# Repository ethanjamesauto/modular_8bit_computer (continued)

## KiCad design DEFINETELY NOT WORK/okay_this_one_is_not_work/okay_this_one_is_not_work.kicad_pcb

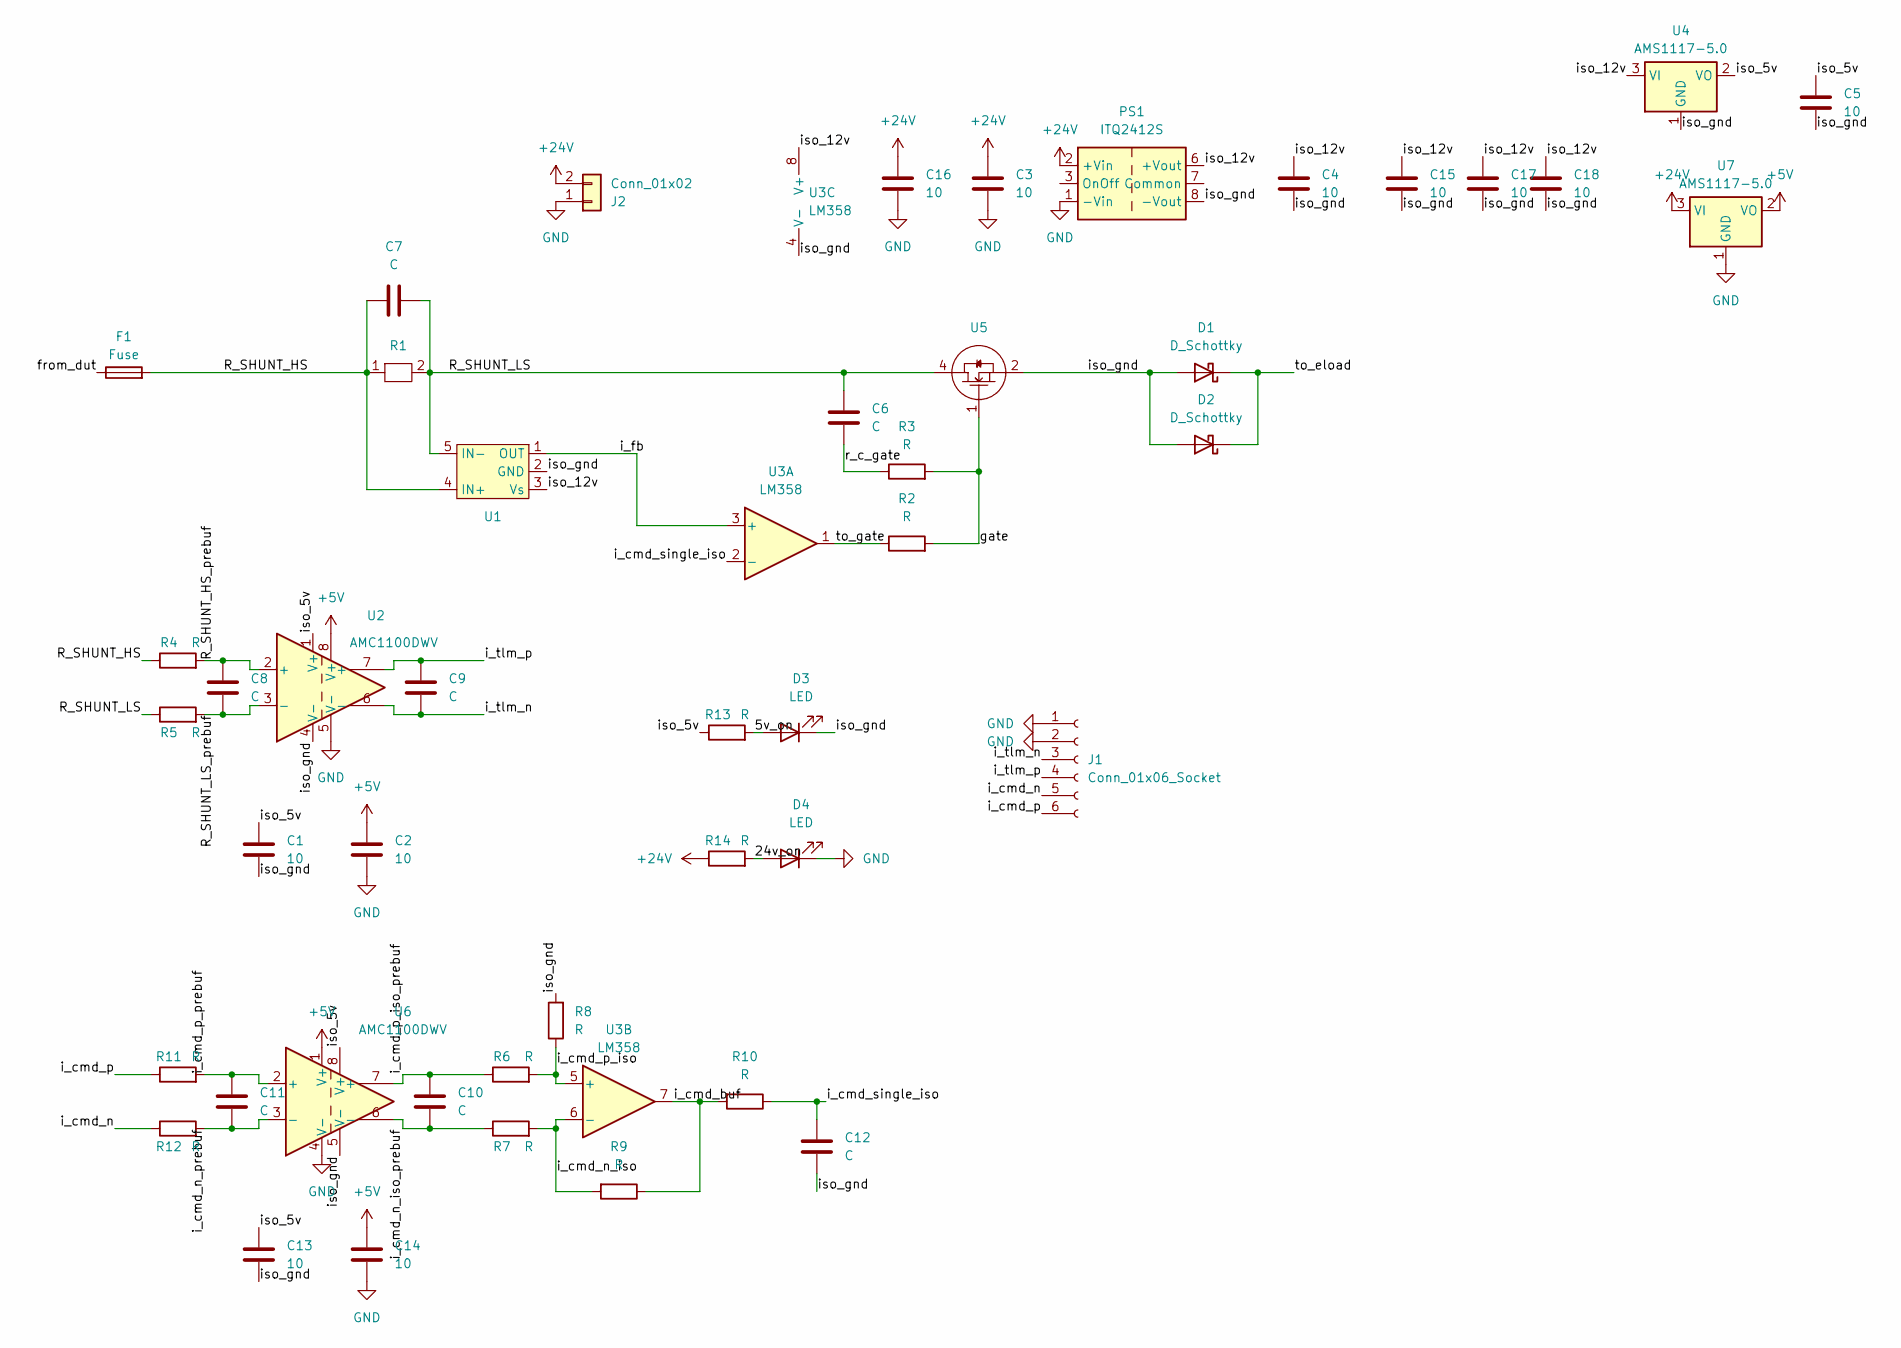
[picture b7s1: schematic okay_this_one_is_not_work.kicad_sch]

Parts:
C1, C2, C3, C4, C5, C13, C14, C15, C16, C17, C18: 10; C_1206_3216Metric_Pad1.33x1.80mm_HandSolder
C6, C7, C8, C9, C10, C11, C12: C; C_0603_1608Metric_Pad1.08x0.95mm_HandSolder
D1, D2: D_Schottky; D_PowerDI-5
D3, D4: LED; LED_0603_1608Metric_Pad1.05x0.95mm_HandSolder
F1: Fuse; Fuse_Schurter_UMT250
J1: Conn_01x06_Socket; PinHeader_1x06_P2.54mm_Vertical
J2: Conn_01x02; PhoenixContact_SPT_2.5_2-H-5.0_1x02_P5.0mm_Horizontal
PS1: ITQ2412S; Converter_DCDC_XP_POWER-ITxxxxxS_THT
R1: 4527
R2, R3, R4, R5, R6, R7, R8, R9, R10, R11, R12, R13, R14: R; R_0603_1608Metric_Pad0.98x0.95mm_HandSolder
U1: SOT-23-5_HandSoldering
U2, U6: AMC1100DWV; SOIC-8_7.5x5.85mm_P1.27mm
U3: LM358; SOIC-8_3.9x4.9mm_P1.27mm
U4, U7: AMS1117-5.0; SOT-223-3_TabPin2
U5: TO-263-6

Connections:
+5V: C2.1, C14.1, U2.8 (V+), U6.1 (V+), U7.2 (VO)
+24V: C3.1, C16.1, J2.2, PS1.2 (+Vin), R14.1, U7.3 (VI)
/5v_on: D3.2 (A), R13.2
/24v_on: D4.2 (A), R14.2
/R_SHUNT_HS: C7.1, F1.2, R1.1, R4.1, U1.4 (IN+)
/R_SHUNT_HS_prebuf: C8.1, R4.2, U2.2 (+)
/R_SHUNT_LS: C6.1, C7.2, R1.2, R5.1, U1.5 (IN-), U5.4
/R_SHUNT_LS_prebuf: C8.2, R5.2, U2.3 (-)
/from_dut: F1.1
/gate: R2.2, R3.2, U5.1
/i_cmd_buf: R9.1, R10.2, U3.7
/i_cmd_n: J1.5, R12.1
/i_cmd_n_iso: R7.2, R9.2, U3.6 (-)
/i_cmd_n_iso_prebuf: C10.2, R7.1, U6.6 (-)
/i_cmd_n_prebuf: C11.2, R12.2, U6.3 (-)
/i_cmd_p: J1.6, R11.1
/i_cmd_p_iso: R6.2, R8.1, U3.5 (+)
/i_cmd_p_iso_prebuf: C10.1, R6.1, U6.7 (+)
/i_cmd_p_prebuf: C11.1, R11.2, U6.2 (+)
/i_cmd_single_iso: C12.1, R10.1, U3.2 (-)
/i_fb: U1.1 (OUT), U3.3 (+)
/i_tlm_n: C9.2, J1.3, U2.6 (-)
/i_tlm_p: C9.1, J1.4, U2.7 (+)
/iso_5v: C1.1, C5.1, C13.1, R13.1, U2.1 (V+), U4.2 (VO), U6.8 (V+)
/iso_12v: C4.1, C15.1, C17.1, C18.1, PS1.6 (+Vout), U1.3 (Vs), U3.8 (V+), U4.3 (VI)
/iso_gnd: C1.2, C4.2, C5.2, C12.2, C13.2, C15.2, C17.2, C18.2, D1.2 (A), D2.2 (A), D3.1 (K), PS1.8 (-Vout), R8.2, U1.2 (GND), U2.4 (V-), U3.4 (V-), U4.1 (GND), U5.2, U5.3, U5.5, U5.6, U5.7, U6.5 (V-)
/r_c_gate: C6.2, R3.1
/to_eload: D1.1 (K), D2.1 (K)
/to_gate: R2.1, U3.1
GND: C2.2, C3.2, C14.2, C16.2, D4.1 (K), J1.1, J1.2, J2.1, PS1.1 (-Vin), U2.5 (V-), U6.4 (V-), U7.1 (GND)

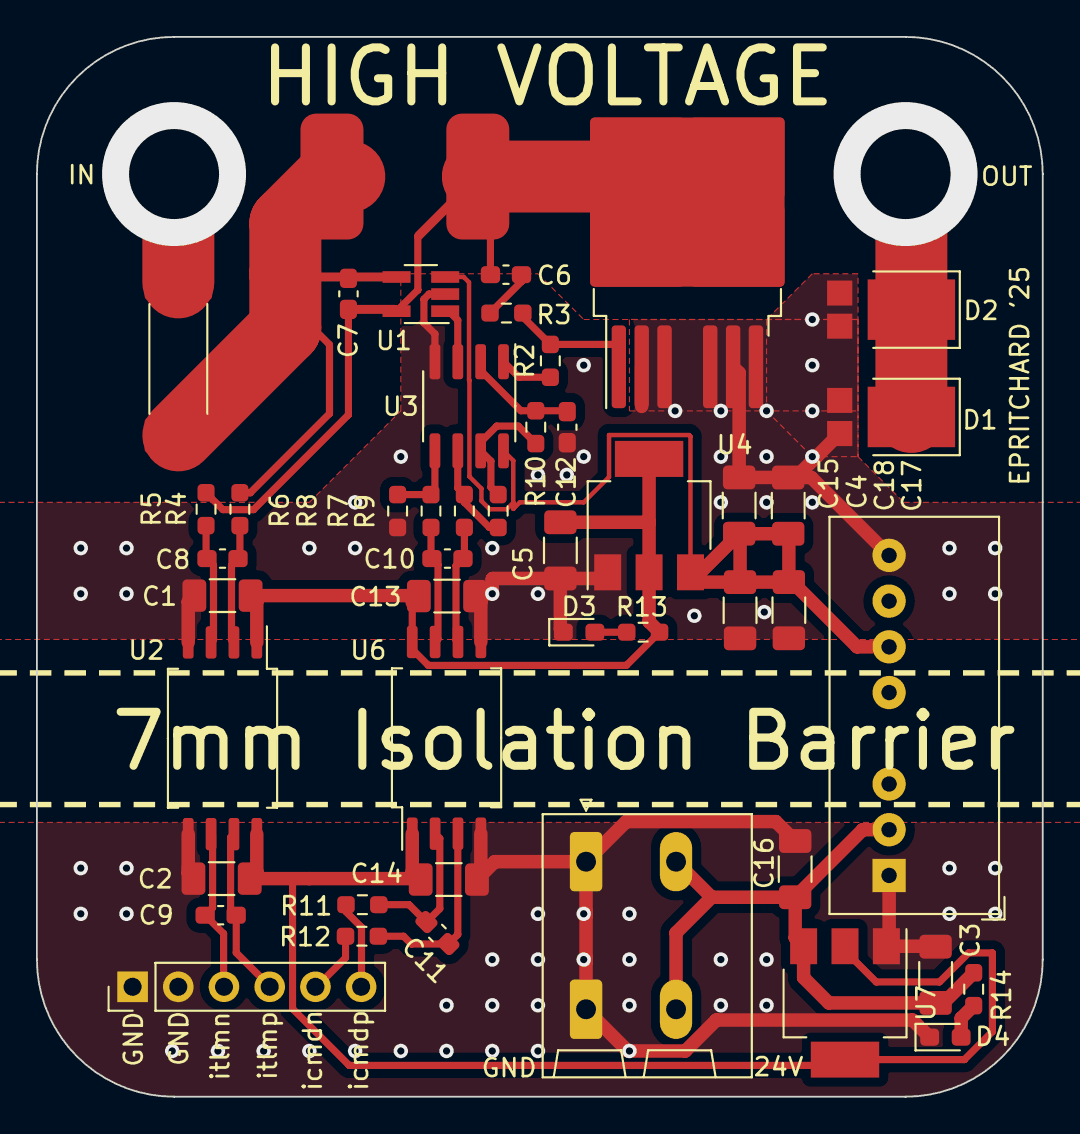
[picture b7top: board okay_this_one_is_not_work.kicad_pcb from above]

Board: 2 copper layers, 55.9 x 58.9 mm, 47 parts (0 on the bottom side), 29 nets.

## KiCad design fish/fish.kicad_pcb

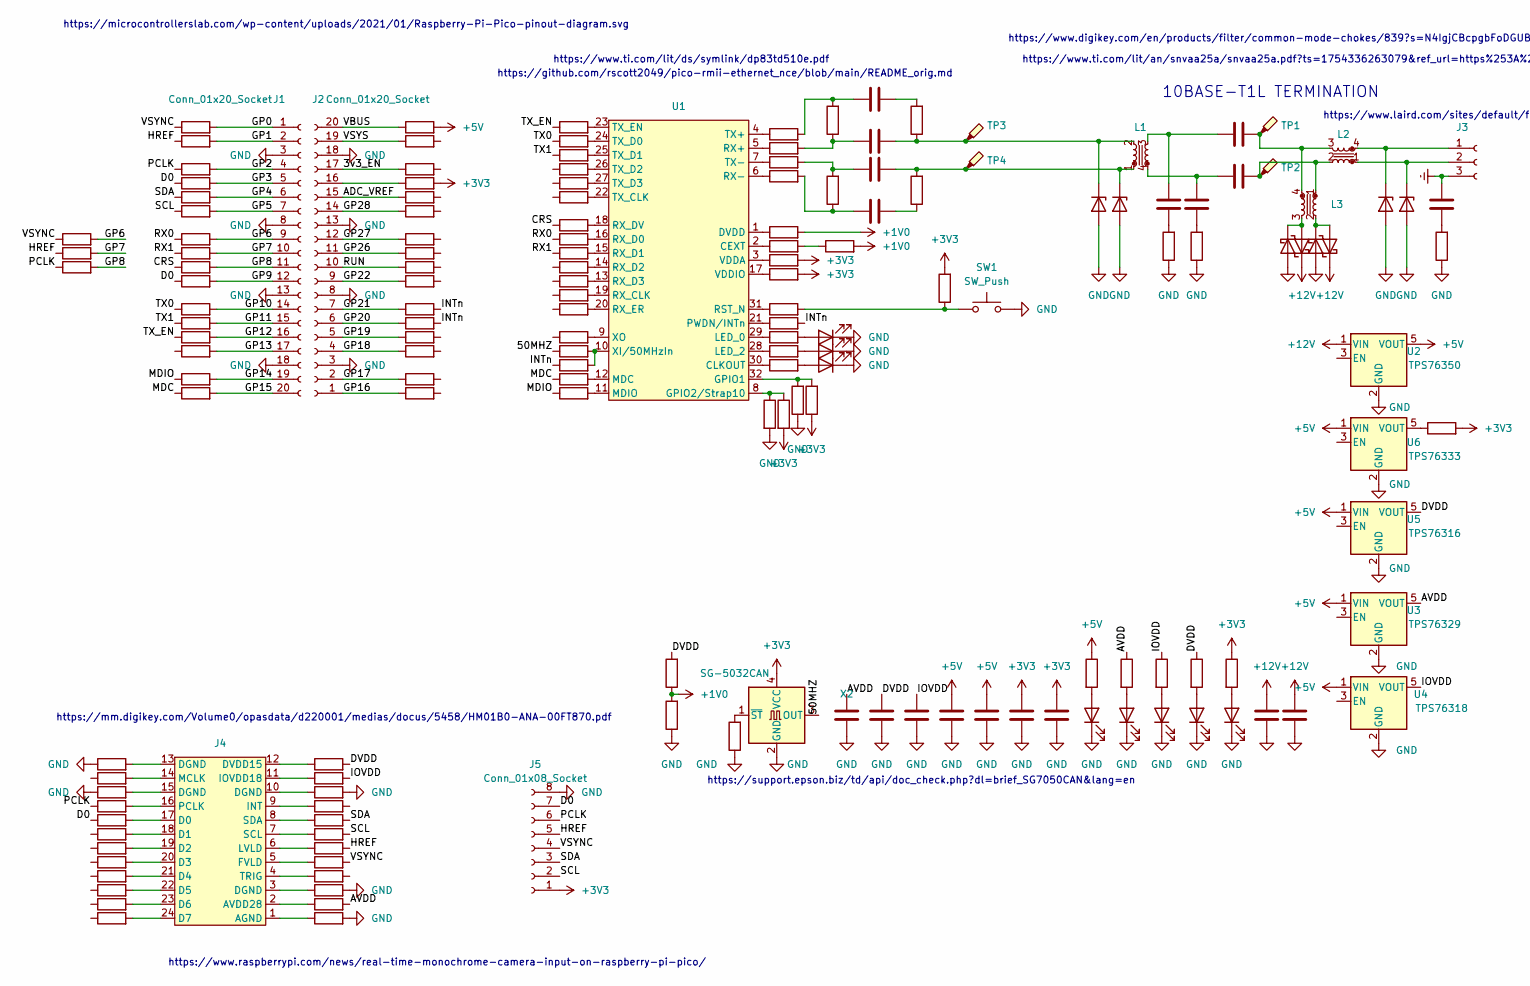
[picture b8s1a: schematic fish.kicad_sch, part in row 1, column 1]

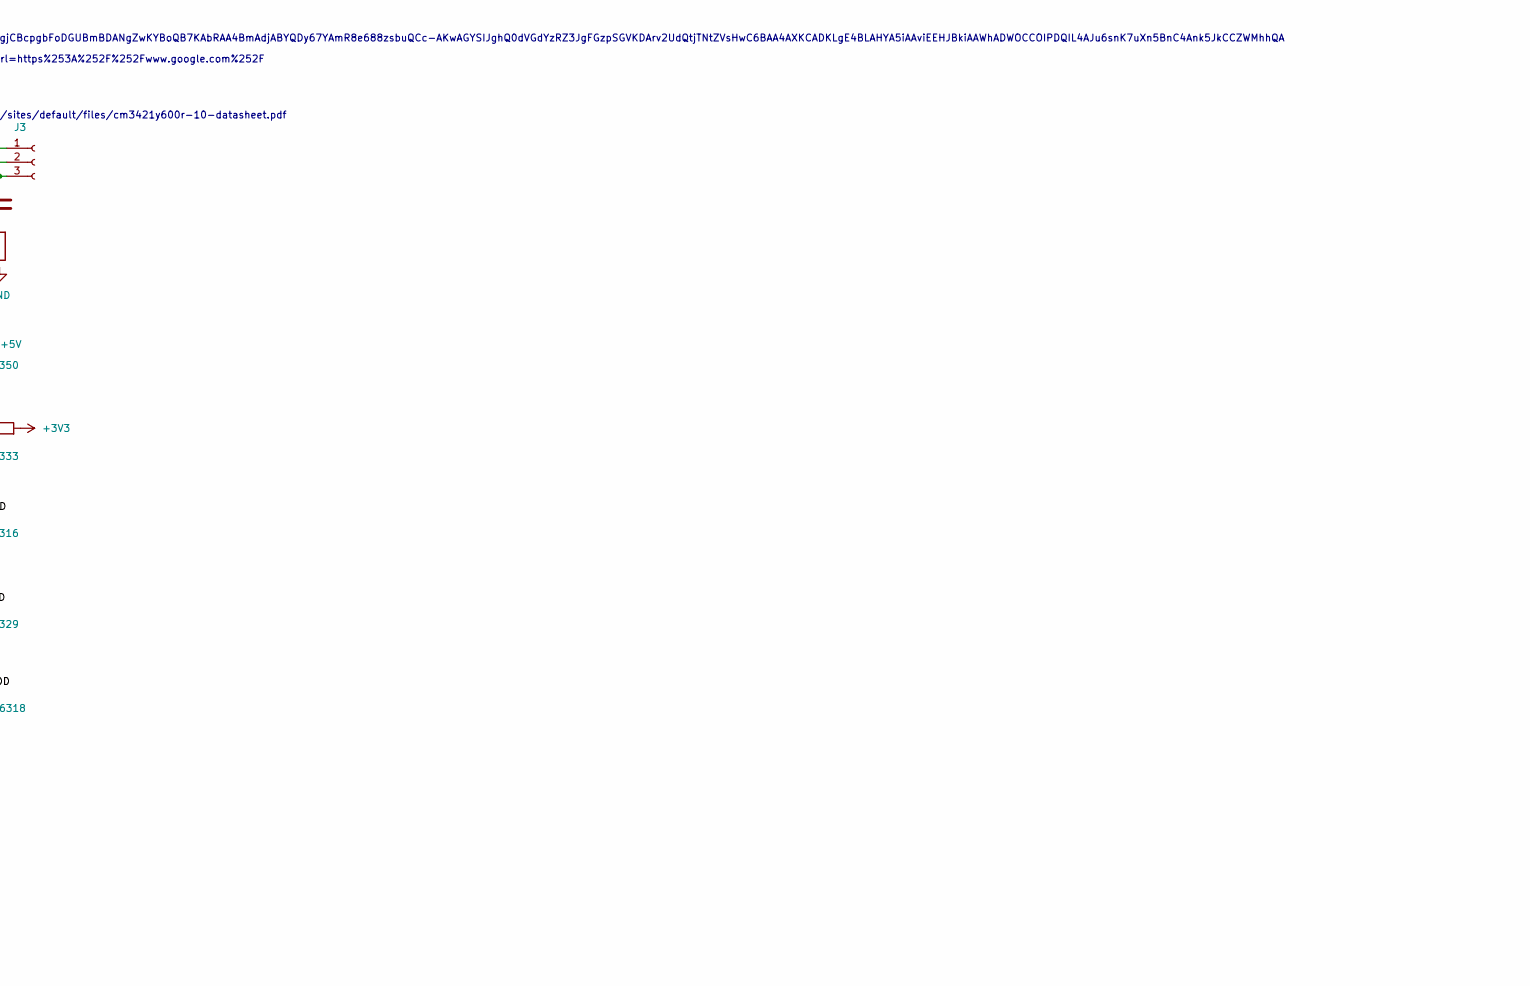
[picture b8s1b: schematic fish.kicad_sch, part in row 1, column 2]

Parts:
C1, C2, C3, C4, C5, C6, C7, C8, C9, C10, C11, C12, C13, C14, C15, C16: C; C_0603_1608Metric_Pad1.08x0.95mm_HandSolder
C17, C18: C; C_1206_3216Metric_Pad1.33x1.80mm_HandSolder
D1, D2, D3, D12, D13, D14, D15, D16: LED; LED_0603_1608Metric_Pad1.05x0.95mm_HandSolder
D4, D5, D6, D7: D_Schottky; D_2010_5025Metric_Pad1.52x2.65mm_HandSolder
D8, D9, D10, D11: D_Zener; D_0603_1608Metric_Pad1.05x0.95mm_HandSolder
J1, J2: Conn_01x20_Socket; PinHeader_1x20_P2.54mm_Vertical
J3: Conn_01x03_Socket; PinHeader_1x03_P2.54mm_Vertical
J4: Molex_SlimStack_502426-2410_2x12_P0.40mm_Vertical
J5: Conn_01x08_Socket; PinHeader_1x08_P2.54mm_Vertical
L1, L2, L3: L_Iron_Coupled_Small_1243; Pulse_PA2001NL
R1, R2, R3, R4, R5, R6, R7, R8, R9, R10, R11, R12, R13, R14, R15, R16, R17, R18, R19, R20, R21, R22, R23, R24, R25, R26, R27, R28, R29, R30, R31, R32, R33, R34, R35, R36, R37, R38, R39, R40, R41, R42, R43, R44, R45, R46, R47, R48, R49, R50, R51, R52, R53, R54, R55, R56, R57, R58, R59, R60, R61, R62, R63, R64, R65, R66, R67, R68, R69, R70, R71, R72, R73, R74, R75, R76, R77, R78, R79, R80, R81, R82, R83, R84, R85, R86, R87, R88, R89, R90, R91, R92, R93, R94, R95, R96, R97, R98, R99, R100, R101, R102, R103, R104, R105, R106, R107, R108, R109, R110: 0; R_0603_1608Metric_Pad0.98x0.95mm_HandSolder
R111, R112: 0; R_1206_3216Metric_Pad1.30x1.75mm_HandSolder
SW1: SW_Push; SW_DIP_SPSTx01_Slide_6.7x4.1mm_W6.73mm_P2.54mm_LowProfile_J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
TP1, TP2, TP3, TP4: TestPoint_Probe; TestPoint_Pad_D1.0mm
U1: VQFN-32-1EP_5x5mm_P0.5mm_EP3.1x3.1mm_ThermalVias
U2: TPS76350; SOT-23-5
U3: TPS76329; SOT-23-5
U4: TPS76318; SOT-23-5
U5: TPS76316; SOT-23-5
U6: TPS76333; SOT-23-5
X2: SG-5032CAN; Oscillator_SMD_SeikoEpson_SG8002LB-4Pin_5.0x3.2mm

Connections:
+1V0: R54.2, R68.2, R111.1, R112.2
+3V3: C15.1, C16.1, J5.1, R29.2, R56.2, R57.2, R65.2, R66.1, R69.2, R107.2, R108.1, X2.4 (VCC)
+5V: C13.1, C14.1, R32.2, R103.1, U2.5 (VOUT), U3.1 (VIN), U4.1 (VIN), U5.1 (VIN), U6.1 (VIN)
+12V: C17.2, C18.2, D4.1 (K), D5.1 (K), U2.1 (VIN)
/3v3_EN: J2.17, R30.1
/50MHZ: R47.1, X2.3 (OUT)
/ADC_VREF: J2.15, R28.1
/AVDD: C10.1, R86.2, R104.1, U3.5 (VOUT)
/CRS: R9.1, R39.1
/D0: J5.7, R4.1, R10.1, R95.1
/DVDD: C11.1, R76.2, R106.1, R111.2, U5.5 (VOUT)
/GP0: J1.1, R1.2
/GP1: J1.2, R2.2
/GP2: J1.4, R3.2
/GP3: J1.5, R4.2
/GP4: J1.6, R5.2
/GP5: J1.7, R6.2
/GP6: J1.9, R7.2, R100.2
/GP7: J1.10, R8.2, R101.2
/GP8: J1.11, R9.2, R102.2
/GP9: J1.12, R10.2
/GP10: J1.14, R11.2
/GP11: J1.15, R12.2
/GP12: J1.16, R13.2
/GP13: J1.17, R14.2
/GP14: J1.19, R15.2
/GP15: J1.20, R16.2
/GP16: J2.1, R17.1
/GP17: J2.2, R18.1
/GP18: J2.4, R19.1
/GP19: J2.5, R20.1
/GP20: J2.6, R21.1
/GP21: J2.7, R22.1
/GP22: J2.9, R23.1
/GP26: J2.11, R25.1
/GP27: J2.12, R26.1
/GP28: J2.14, R27.1
/HREF: J5.5, R2.1, R82.2, R101.1
/INTn: R21.2, R22.2, R59.2, R110.1
/IOVDD: C12.1, R77.2, R105.1, U4.5 (VOUT)
/MDC: R16.1, R48.1
/MDIO: R15.1, R49.1
/PCLK: J5.6, R3.1, R96.1, R102.1
/RUN: J2.10, R24.1
/RX0: R7.1, R40.1
/RX1: R8.1, R41.1
/SCL: J5.2, R6.1, R81.2
/SDA: J5.3, R5.1, R80.2
/TX0: R11.1, R34.1
/TX1: R12.1, R35.1
/TX_EN: R13.1, R33.1
/VBUS: J2.20, R32.1
/VSYNC: J5.4, R1.1, R83.2, R100.1
/VSYS: J2.19, R31.1
Earth: C9.2, J3.3
GND: C10.2, C11.2, C12.2, C13.2, C14.2, C15.2, C16.2, C17.1, C18.1, D1.1 (K), D2.1 (K), D3.1 (K), D6.2 (A), D7.2 (A), D8.2 (A), D9.2 (A), D10.2 (A), D11.2 (A), D12.1 (K), D13.1 (K), D14.1 (K), D15.1 (K), D16.1 (K), J1.3, J1.8, J1.13, J1.18, J2.3, J2.8, J2.13, J2.18, J5.8, R63.1, R64.2, R73.1, R74.1, R75.1, R78.2, R85.2, R87.2, R97.1, R99.1, R109.1, R112.1, SW1.2, U2.2 (GND), U3.2 (GND), U4.2 (GND), U5.2 (GND), U6.2 (GND), X2.2 (GND)
unnamed: C1.2, R51.2, R67.1
unnamed: C2.1, R52.2, R70.2
unnamed: C3.1, R53.2, R70.1
unnamed: C3.2, R72.1
unnamed: C4.1, R71.2
unnamed: C4.2, R50.2, R67.2
unnamed: C5.1, L2.3, L3.4, TP1.1
unnamed: C5.2, C7.2, L1.3
unnamed: C6.1, L2.2, L3.1, TP2.1
unnamed: C6.2, C8.2, L1.4
unnamed: C7.1, R73.2
unnamed: C8.1, R74.2
unnamed: C9.1, R75.2
unnamed: D1.2 (A), R61.2
unnamed: D2.2 (A), R62.2
unnamed: D3.2 (A), R60.2
unnamed: D4.2 (A), D6.1 (K), L3.2
unnamed: D5.2 (A), D7.1 (K), L3.3
unnamed: C1.1, D8.1 (K), L1.2, R71.1, TP3.1
unnamed: C2.2, D9.1 (K), L1.1, R72.2, TP4.1
unnamed: D10.1 (K), J3.1, L2.4
unnamed: D11.1 (K), J3.2, L2.1
unnamed: D12.2 (A), R103.2
unnamed: D13.2 (A), R104.2
unnamed: D14.2 (A), R105.2
unnamed: D15.2 (A), R106.2
unnamed: D16.2 (A), R108.2
unnamed: J2.16, R29.1
unnamed: J4.1 (AGND), R87.1
unnamed: J4.2 (AVDD28), R86.1
unnamed: J4.17 (D0), R95.2
unnamed: J4.18 (D1), R94.2
unnamed: J4.19 (D2), R93.2
unnamed: J4.20 (D3), R92.2
unnamed: J4.21 (D4), R91.2
unnamed: J4.22 (D5), R90.2
unnamed: J4.23 (D6), R89.2
unnamed: J4.24 (D7), R88.2
unnamed: J4.3 (DGND), R85.1
unnamed: J4.10 (DGND), R78.1
unnamed: J4.13 (DGND), R99.2
unnamed: J4.15 (DGND), R97.2
unnamed: J4.12 (DVDD15), R76.1
unnamed: J4.5 (FVLD), R83.1
unnamed: J4.9 (INT), R79.1
unnamed: J4.11 (IOVDD18), R77.1
unnamed: J4.6 (LVLD), R82.1
unnamed: J4.14 (MCLK), R98.2
unnamed: J4.16 (PCLK), R96.2
unnamed: J4.7 (SCL), R81.1
unnamed: J4.8 (SDA), R80.1
unnamed: J4.4 (TRIG), R84.1
unnamed: R55.2, R68.1
unnamed: R58.2, R69.1, SW1.1
unnamed: R55.1, U1.2 (CEXT)
unnamed: R61.1, U1.30 (CLKOUT)
unnamed: R54.1, U1.1 (DVDD)
unnamed: R63.2, R66.2, U1.32 (GPIO1)
unnamed: R64.1, R65.1, U1.8 (GPIO2/Strap10)
unnamed: R60.1, U1.29 (LED_0)
unnamed: R62.1, U1.28 (LED_2)
unnamed: R48.2, U1.12 (MDC)
unnamed: R49.2, U1.11 (MDIO)
unnamed: R59.1, U1.21 (PWDN/INTn)
unnamed: R58.1, U1.31 (RST_N)
unnamed: R51.1, U1.5 (RX+)
unnamed: R53.1, U1.6 (RX-)
unnamed: R44.2, U1.19 (RX_CLK)
unnamed: R40.2, U1.16 (RX_D0)
unnamed: R41.2, U1.15 (RX_D1)
unnamed: R42.2, U1.14 (RX_D2)
unnamed: R43.2, U1.13 (RX_D3)
unnamed: R39.2, U1.18 (RX_DV)
unnamed: R45.2, U1.20 (RX_ER)
unnamed: R50.1, U1.4 (TX+)
unnamed: R52.1, U1.7 (TX-)
unnamed: R38.2, U1.22 (TX_CLK)
unnamed: R34.2, U1.24 (TX_D0)
unnamed: R35.2, U1.25 (TX_D1)
unnamed: R36.2, U1.26 (TX_D2)
unnamed: R37.2, U1.27 (TX_D3)
unnamed: R33.2, U1.23 (TX_EN)
unnamed: R56.1, U1.3 (VDDA)
unnamed: R57.1, U1.17 (VDDIO)
unnamed: R47.2, R110.2, U1.10 (XI/50MHzIn)
unnamed: R46.2, U1.9 (XO)
unnamed: R107.1, U6.5 (VOUT)
unnamed: R109.2, X2.1 (~ST)

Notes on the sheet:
https://www.raspberrypi.com/news/real-time-monochrome-camera-input-on-raspberry-pi-pico/
https://www.laird.com/sites/default/files/cm3421y600r-10-datasheet.pdf
https://microcontrollerslab.com/wp-content/uploads/2021/01/Raspberry-Pi-Pico-pinout-diagram.svg
https://github.com/rscott2049/pico-rmii-ethernet_nce/blob/main/README_orig.md
https://support.epson.biz/td/api/doc_check.php?dl=brief_SG7050CAN&lang=en
https://www.digikey.com/en/products/filter/common-mode-chokes/839?s=N4IgjCBcpgbFoDGUBmBDANgZwKYBoQB7KAbRAA4BmAdjABYQDy67YAmR8e688zsbuQCc-AKwAGYSIJghQ0dVGdYzRZ3JgFGzpSGVKDArv2UdQtjTNtZVsHwC6BAA4AXKCADKLgE4BLAHYA5iAAviEEHJBkiAAWhADWOCCOIPDQIL4AJu6snK7uXn5BnC4Ank5JkCCZWMhhQA
10BASE-T1L TERMINATION
https://www.ti.com/lit/an/snvaa25a/snvaa25a.pdf?ts=1754336263079&ref_url=https%253A%252F%252Fwww.google.com%252F
https://www.ti.com/lit/ds/symlink/dp83td510e.pdf
https://mm.digikey.com/Volume0/opasdata/d220001/medias/docus/5458/HM01B0-ANA-00FT870.pdf

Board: 2 copper layers, 166 parts (0 on the bottom side), 144 nets, no tracks yet.

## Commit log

2024-08-18 Add some digital 74 series wrappers
2024-08-18 Update docs
2024-08-19 Processor
    check out the processor. Grinded on this for all of sunday, I thought i would get it done and ordered but I actually want to verify the DRCs on this one so holding off.
    This one needs control lines to be soldered by hand as although I have a general idea of the instructions I'm not confident enough to put them in traces.
    Should finish this up tmr and order tmr night along with the 74ls245 buffer thingy.
2024-08-20 pushing processor rev1
    Piss Quiet reference
2024-08-27 Add LED card
2024-08-28 Add led card arduino test
2024-08-28 Update led test
2024-08-29 hellop ccp
    FUCK
2024-08-31 Add digital models
2024-08-31 Update bus spec
2024-08-31 Change wire names
2024-08-31 Add dumb card for testing verilog-kicad
2024-09-02 Add my DD2 project cuz it's useful here
2024-09-02 Add images
2024-09-02 Add simulation files
2024-09-02 Update bus spec in sim
2024-09-03 Creenis
    Cnreenis
2024-09-04 Add shift card
2024-09-06 Add card for verilog-kicad
2024-09-10 processor redesign work
    redesign
2024-09-10 Pacheck RF board
    Pacheck RF Board
2024-09-11 hah poop
    push
2024-09-11 psuh
    pshu
2024-09-17 Add code to display characters on led card
2024-09-19 Add images of atx mobo
2024-09-24 pushing a bunch of new projects
    new pcbs
2024-09-25 stepper cnc
    stepper cnc
2024-09-25 centering pcb above origin not below
    centering pcb above origin not below
2024-09-25 pcb errors
    pcb errors
2024-09-25 moving board
    moving board
2024-09-25 seems like it didnt update
    didnt update
2024-09-25 new updates
    new updates
2024-09-25 new format
    new format
2024-09-25 g9oot do dps
    asdfs
2024-09-26 mini version
    mini
2024-09-26 rotate 90 degrees
    reat
2024-09-26 move right
    fdsaf
2024-09-26 gerber
    gerber
2024-09-27 pachcok
2024-09-27 sadfj
2024-09-30 test cnc
2024-10-08 YOSKRIBBA
2024-10-17 psunoig
2024-11-03 93c46a stuff
2024-11-04 cnc 93c46a
2024-11-04 pushing the way I know to use denford gcode plotter
2024-11-20 se
    se
